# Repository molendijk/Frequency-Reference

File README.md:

# 10MHz Frequency Reference Distributor and 25MHz generator and distributor.

  ## Purpose
  
  This hardware project is intended for people posessing a 10MHz sinusoidal reference oscillator (GPS DO / Rubidium Source) 
  but require a 25MHz reference for use with an SDR (Adalm-Pluto), ADF4351 (Evaluation board) or a 
  LNB (modified Bulls-Eye).
  
  https://www.analog.com/en/resources/evaluation-hardware-and-software/evaluation-boards-kits/adalm-pluto.html
  https://github.com/molendijk/QO100_LO_ADF4351_Loader
  https://3b8mars.org/wp-content/uploads/2023/10/Bulleye-LNB-modification-for-external-clocking-updated-Oct2023.pdf

  ## Implementation

  The circuit first converts the incoming sine-wave to a square-wave. A potentiometer allows to set the square-wave
  duty factor to 50%. This square-wave is then presented to 3 external outputs of which 1 is DC coupled. A 4th internal
  copy is then available internally to be connected to the input of an external 50MHz band-pass filter.
  The 50MHz sinusoidal output of this filter is then connected to the 50MHz input, that is once again transformed to a 
  square-wave and finally divided by 2 to generate 25MHz that is presented to 4 outputs of which 2 are DC coupled.
  
  The circuit also has an interface J6 for the required power supplies (+15V, +5V) for the FE-5650 Rb frequency standard.
  As the FE-5650 module uses a 9 pin Cannon D connector, a special flat-cable with on one side the DB9 F and on the other
  side a 2 x 7 header is needed. The pin correspondances are marked in a table on page 2 of the schematic.
  Note that pin 1 of either connector are aligned (connected).
  
  ## Mounting sequence and Commissioning
  
  ### Preparations
  1. Solder SMD parts on F-side and B-side **EXCEPT: power jumpers R10, R14, R22 and Edge-mount coax connectors**
  2. Solder through-hole parts: potentiometer R15 and U6 regulator, LEDs D1 and D2 (Square pin is the cathode -> short leg).
  ### Power-supply
  3. Connect VBUS to a 16V power-supply and while measuring (with a DVM) the voltage between TP_GND and TP_15V
     trim potentiometer R15 to obtain 15V.
  4. Solder through-hole parts: potentiometers R12, R17 and regulators U2, U3.
  5. Trim potentiometer R17 while measuring TP_P5V to get 5V
  6. Trim potentiometer R12 while measuring TP_P3V3 to get 3.3V
  7. Solder power jumpers: R10, R14 (+5V and +3.3V) and measure the current going into VBUS (IBUS) to be ~30mA. 
  LED D2 should be lit.
  ### 10MHz distributor
  8. Solder Edge-mount SMA coax J1, J2, J3, J4, transistor Q1 and potentiometer R5.
  9. Inject 10MHz ~1.3Vpp in port 10MHz in (J4).
  9. With a DSO (Inputs high-Z) measure the signals at J1, J2 -> ~3.5Vpp AC and J3 -> ~3.5V DC (0 thru +3.5V)
  10. Trim R5 for 50% duty-factor (J1, J2 and J3) Note: V-bias at node C1, R6, R3 will be ~ +1.55V  
  ### 50MHz output
  11. Solder Edge-mount SMA coax J13, through-hole SMA coax: J5, J7, power jumper R22 (+15V, 50MHz gain stage), 
  transistor Q2 and potentiometer R23. 
  12. Connect a previously prepared BPF50 from port BPF50 in (J7) to BPF50 out (J5)
  13. With a DSO (Inputs high-Z) measure the signals on port MHz50 out (J13). -> 50MHz signal ~3.5Vpp AC
  14. Trim R23 for 50% duty-factor 
  ### 25MHz distributor
  15. Solder Edge-mount SMA coax : J9, J10, J11 and J12.
  16. With a DSO (Inputs high-Z) measure the signals on ports J9, J10: 25 MHz DC -> ~3.5V DC (0 thru +3.5V)
  17. With a DSO (Inputs high-Z) measure the signals on ports J11, J12: 25 MHz AC -> ~3.5V AC (50% duty-factor)
 
 Notes: 
  - At the level 17 test configuration IBUS ~0.2A at VBUS +16V
  - Regulator U3 will become hot (70°C) without any heatsink. This may be a good moment to add the heatsink.
  
  18. Connect a flat-cable to J6 and **before connecting the correct Rb reference (FE-5650)**, 
  measure the supply voltages on the DB9 connector.
  
| Pin | Function |
| --- | -------- |
|  1  | +15V     |
|  2  | Gnd +15V |
|  4  | +5V      |
|  5  | Gnd +5V  |
	
  19. Power-down, connect the DB9 side of the flat-cable to the Rb reference, connect the Rb reference 10MHz output
  to J4 the 10MHz input.
  20. Power-up, check supplies, verify and if needed correct the 10MHz 50% duty-factor setting R5. 
  LED D1 should be lit once the Rb reference has reached operating temperature and is frequency locked.
  
  Notes: 
  - The FE-5650 will initially, while heating up, draw >1A from the 15V regulator.
  - The FE-5650 takes a few minutes to heat up and lock to the correct frequency.
  
  ## Trouble shooting
  - In case of no output on the 50MHz port, measure the DC voltages at the outputs of U4 (+3.4V) and U5 (+4.9V).
  If one of these is absent, verify the solder joints of either L1 or L2.
 
  ## Issues with Rev 1.0.0 built 20251031
  - The SMA Edge-mount connector footprints have a greater ground pin spacing than the "standard" Edge-mount SMA
  connectors available. Nevertheless these connectors can be soldered in place, bridging the slight gap between
  the pads and the connector Gnd pins.
  - The TO92 footprint of transistors Q1, Q2 (2N2222) has pin numbering 1,2,3 instead of 3,2,1 (collector emitter swap).
  The workaround is to mount Q1 and Q2 with the flat side opposite to that on the serigraphie.
  - C21 is too close to J6, the 2 x 7 pin header, effectively falling underneath the header plastic. By first mounting
  C21 and then letting the header stick out sufficiently the connector and capacitor can cohabitate.
  - As the 39 nF capacitors are not in the standard series these were replaced by 47 nF capacitors.

  ## Notes
  1. The series terminated DC Coupled outputs are intended to be connected to high-Z (3.3V) logic level inputs.
     The AC Coupled outputs can be terminated in 50 Ohms, typically like when connected to a clock input of an SDR.
  2. The 6th order 50MHz filter is constructed using 3 side-coupled (LC) resonating circuits that yield a good quality factor.
     More details on the construction of this filter will follow soon. 
  3. Certain devices need a sinusoidal 25MHz clock to operate correctly. In this case a simple low-pass filter can
     be used to remove much of the higher harmonics.
  4. Be sure to check permitted input signal levels on 25MHz inputs and if needed, add additional attenuation.

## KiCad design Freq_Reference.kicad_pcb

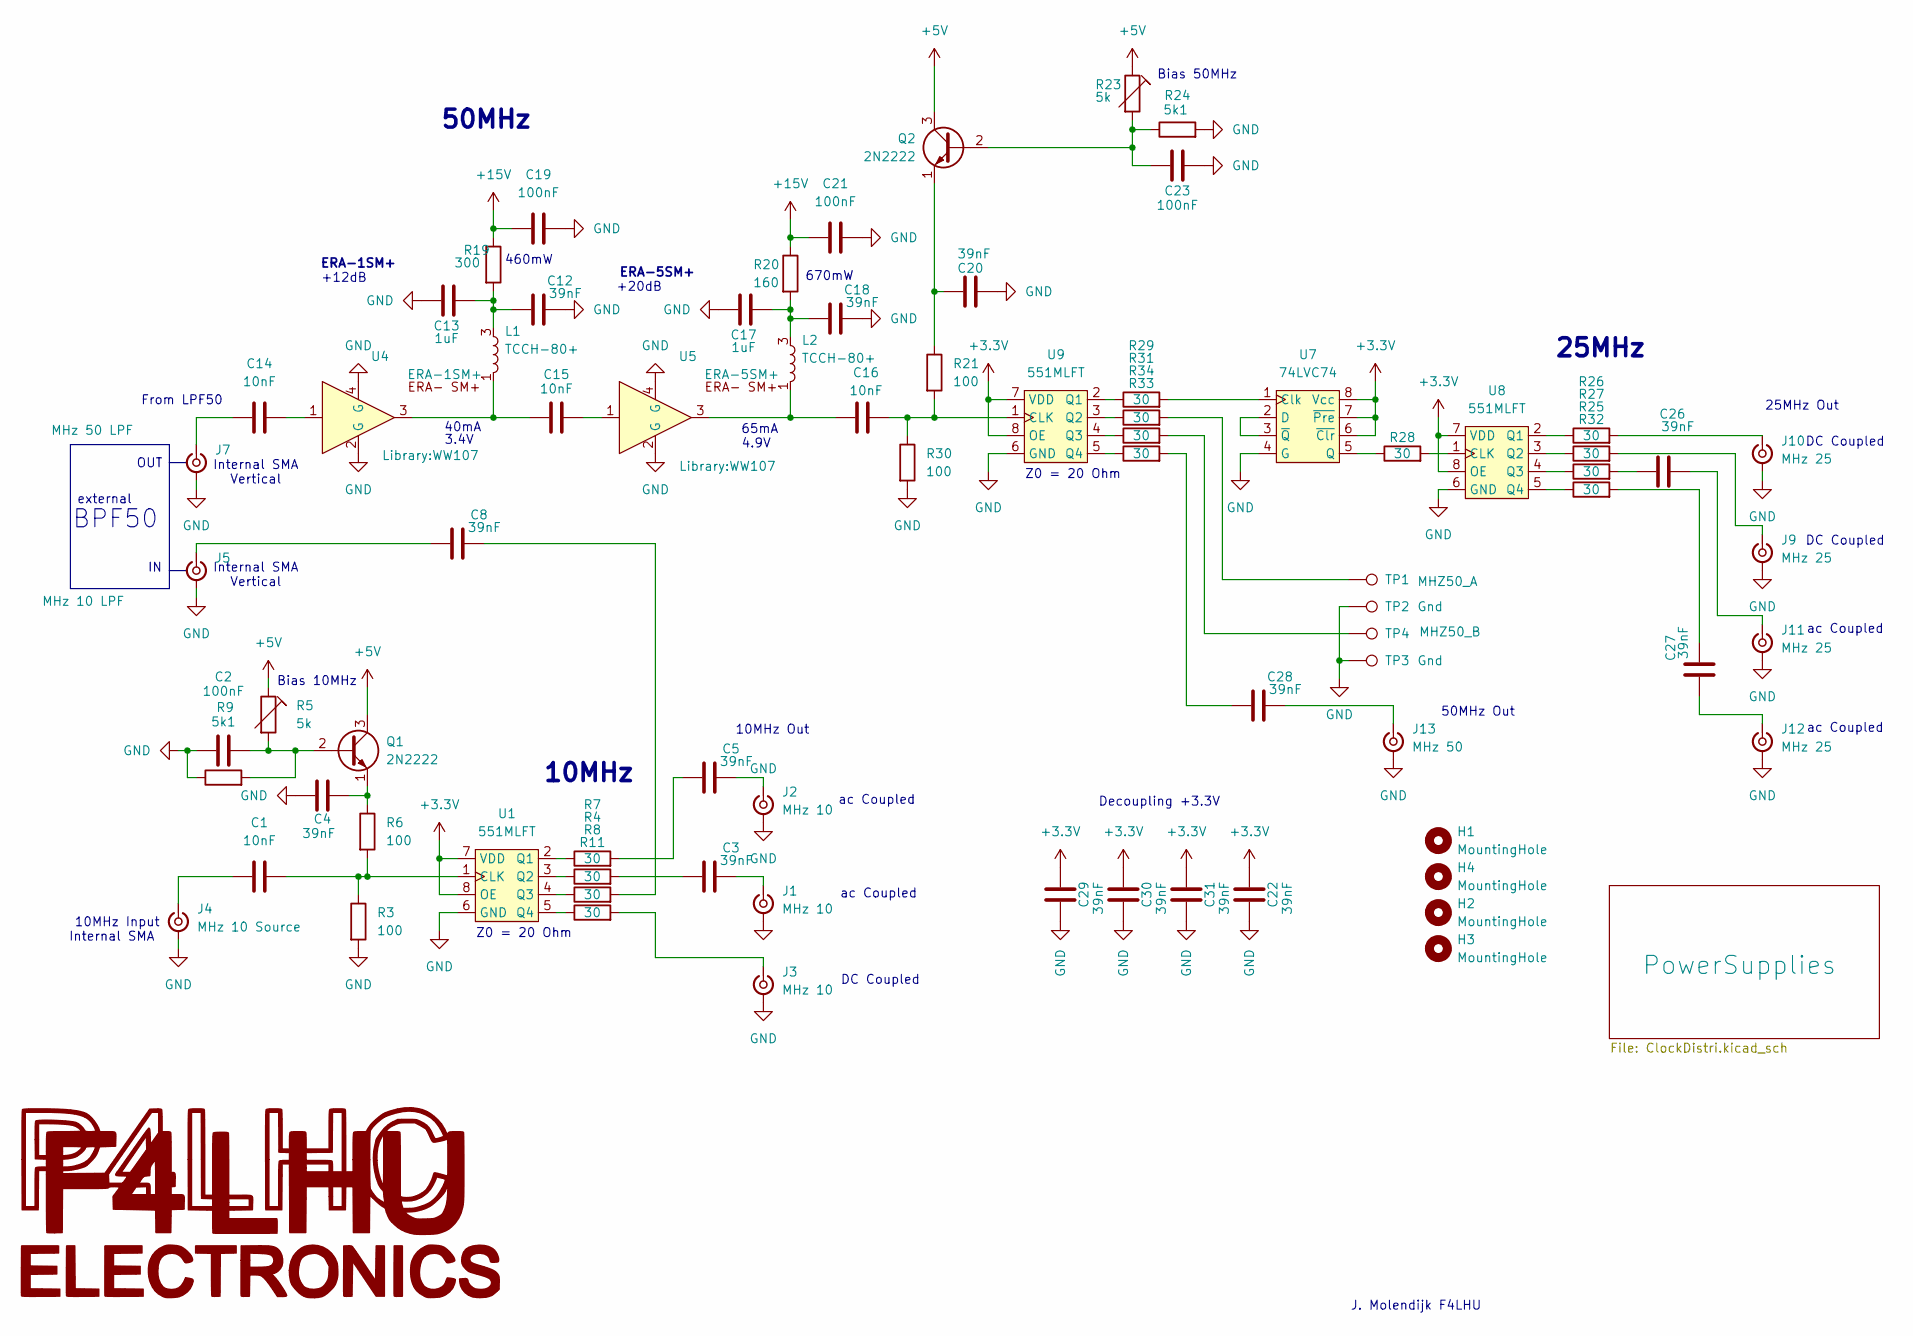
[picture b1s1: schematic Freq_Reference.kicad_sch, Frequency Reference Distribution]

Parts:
C1, C14, C15, C16: 10nF; C_1206_3216Metric_Pad1.33x1.80mm_HandSolder
C2, C19, C21, C23: 100nF; C_1206_3216Metric_Pad1.33x1.80mm_HandSolder
C3, C4, C5, C8, C12, C18, C20, C22, C26, C27, C28, C29, C30, C31: 39nF; C_1206_3216Metric_Pad1.33x1.80mm_HandSolder
C13, C17: 1uF; C_1206_3216Metric_Pad1.33x1.80mm_HandSolder
H1, H2, H3, H4: MountingHole; MountingHole_3.2mm_M3_ISO7380_Pad_TopBottom
J1, J2, J3: MHz 10; SMA_Amphenol_132289_EdgeMount
J4: MHz 10 Source; SMA_Amphenol_132289_EdgeMount
J5: MHz 10 LPF; SMA_Amphenol_132134-11_Vertical
J7: MHz 50 LPF; SMA_Amphenol_132134-11_Vertical
J9, J10, J11, J12: MHz 25; SMA_Amphenol_132289_EdgeMount
J13: MHz 50; SMA_Amphenol_132289_EdgeMount
L1, L2: TCCH-80+; Minicircuits_GU1604
Logo1: LOGO; F4LHU
Q1, Q2: 2N2222; TO-92_Inline_Wide
R3, R6, R21, R30: 100; R_1206_3216Metric_Pad1.30x1.75mm_HandSolder
R4, R7, R8, R11, R25, R26, R27, R28, R29, R31, R32, R33, R34: 30; R_1206_3216Metric_Pad1.30x1.75mm_HandSolder
R5, R23: 5k; Potentiometer_Bourns_3299W_Vertical
R9, R24: 5k1; R_1206_3216Metric_Pad1.30x1.75mm_HandSolder
R19: 300; R_2512_6332Metric_Pad1.40x3.35mm_HandSolder
R20: 160; R_2512_6332Metric_Pad1.40x3.35mm_HandSolder
TP1: MHZ50_A; TestPoint_THTPad_1.5x1.5mm_Drill0.7mm
TP2, TP3: Gnd; TestPoint_THTPad_1.5x1.5mm_Drill0.7mm
TP4: MHZ50_B; TestPoint_THTPad_1.5x1.5mm_Drill0.7mm
U1, U8, U9: 551MLFT; SOIC-8_5.3x6.2mm_P1.27mm
U4: ERA-1SM+; WW107
U5: ERA-5SM+; WW107
U7: 74LVC74; SSOP-8_2.95x2.8mm_P0.65mm

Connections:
+3.3V: C22.1, C29.1, C30.1, C31.1, U1.7 (VDD), U1.8 (OE), U7.6 (~Clr), U7.7 (~Pre), U7.8 (Vcc), U8.7 (VDD), U8.8 (OE), U9.7 (VDD), U9.8 (OE); also elsewhere on the board
+5V: Q1.3 (C), Q2.3 (C), R5.1, R23.1; also elsewhere on the board
+15V: C19.1, C21.1, R19.1, R20.1; also elsewhere on the board
GND: C2.1, C4.2, C12.2, C13.1, C17.1, C18.2, C19.2, C20.2, C21.2, C22.2, C23.2, C29.2, C30.2, C31.2, J1.2 (Ext), J2.2 (Ext), J3.2 (Ext), J4.2 (Ext), J5.2 (Ext), J7.2 (Ext), J9.2 (Ext), J10.2 (Ext), J11.2 (Ext), J12.2 (Ext), J13.2 (Ext), R3.2, R9.1, R24.2, R30.2, TP2.1, TP3.1, U1.6 (GND), U4.2 (G), U4.4 (G), U5.2 (G), U5.4 (G), U7.4 (G), U8.6 (GND), U9.6 (GND); also elsewhere on the board
unnamed: C3.1, R4.2
unnamed: C5.1, R7.2
unnamed: C8.2, R8.2
unnamed: C14.2, U4.1
unnamed: C15.2, U5.1
unnamed: C26.1, R25.2
unnamed: C27.2, R32.2
unnamed: C28.1, R33.2
unnamed: C3.2, J1.1 (In)
unnamed: C5.2, J2.1 (In)
unnamed: J3.1 (In), R11.2
unnamed: C1.1, J4.1 (In)
unnamed: C8.1, J5.1 (In)
unnamed: C14.1, J7.1 (In)
unnamed: J9.1 (In), R27.2
unnamed: J10.1 (In), R26.2
unnamed: C26.2, J11.1 (In)
unnamed: C27.1, J12.1 (In)
unnamed: C28.2, J13.1 (In)
unnamed: C12.1, C13.2, L1.3 (DC), R19.2
unnamed: C15.1, L1.1 (RF-DC), U4.3
unnamed: C17.2, C18.1, L2.3 (DC), R20.2
unnamed: C16.1, L2.1 (RF-DC), U5.3
unnamed: C2.2, Q1.2 (B), R5.2, R9.2
unnamed: C4.1, Q1.1 (E), R6.1
unnamed: C23.1, Q2.2 (B), R23.2, R24.1
unnamed: C20.1, Q2.1 (E), R21.1
unnamed: R31.2, TP1.1
unnamed: R34.2, TP4.1
unnamed: C1.2, R3.1, R6.2, U1.1 (CLK)
unnamed: R7.1, U1.2 (Q1)
unnamed: R4.1, U1.3 (Q2)
unnamed: R8.1, U1.4 (Q3)
unnamed: R11.1, U1.5 (Q4)
unnamed: R29.2, U7.1 (Clk)
unnamed: U7.2 (D), U7.3 (~Q)
unnamed: R28.1, U7.5 (Q)
unnamed: R28.2, U8.1 (CLK)
unnamed: R26.1, U8.2 (Q1)
unnamed: R27.1, U8.3 (Q2)
unnamed: R25.1, U8.4 (Q3)
unnamed: R32.1, U8.5 (Q4)
unnamed: C16.2, R21.2, R30.1, U9.1 (CLK)
unnamed: R29.1, U9.2 (Q1)
unnamed: R31.1, U9.3 (Q2)
unnamed: R34.1, U9.4 (Q3)
unnamed: R33.1, U9.5 (Q4)

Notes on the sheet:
Z0 = 20 Ohm
10MHz Input
Internal SMA
external
BPF50
670mW
10MHz Out
65mA
ac Coupled
40mA
ERA-1SM+
25MHz
DC Coupled
J. Molendijk F4LHU
Decoupling +3.3V
50MHz
From LPF50
3.4V
Internal SMA Vertical
10MHz
Bias 50MHz
+12dB
460mW
4.9V
OUT
Bias 10MHz
ERA-5SM+
25MHz Out
+20dB
50MHz Out

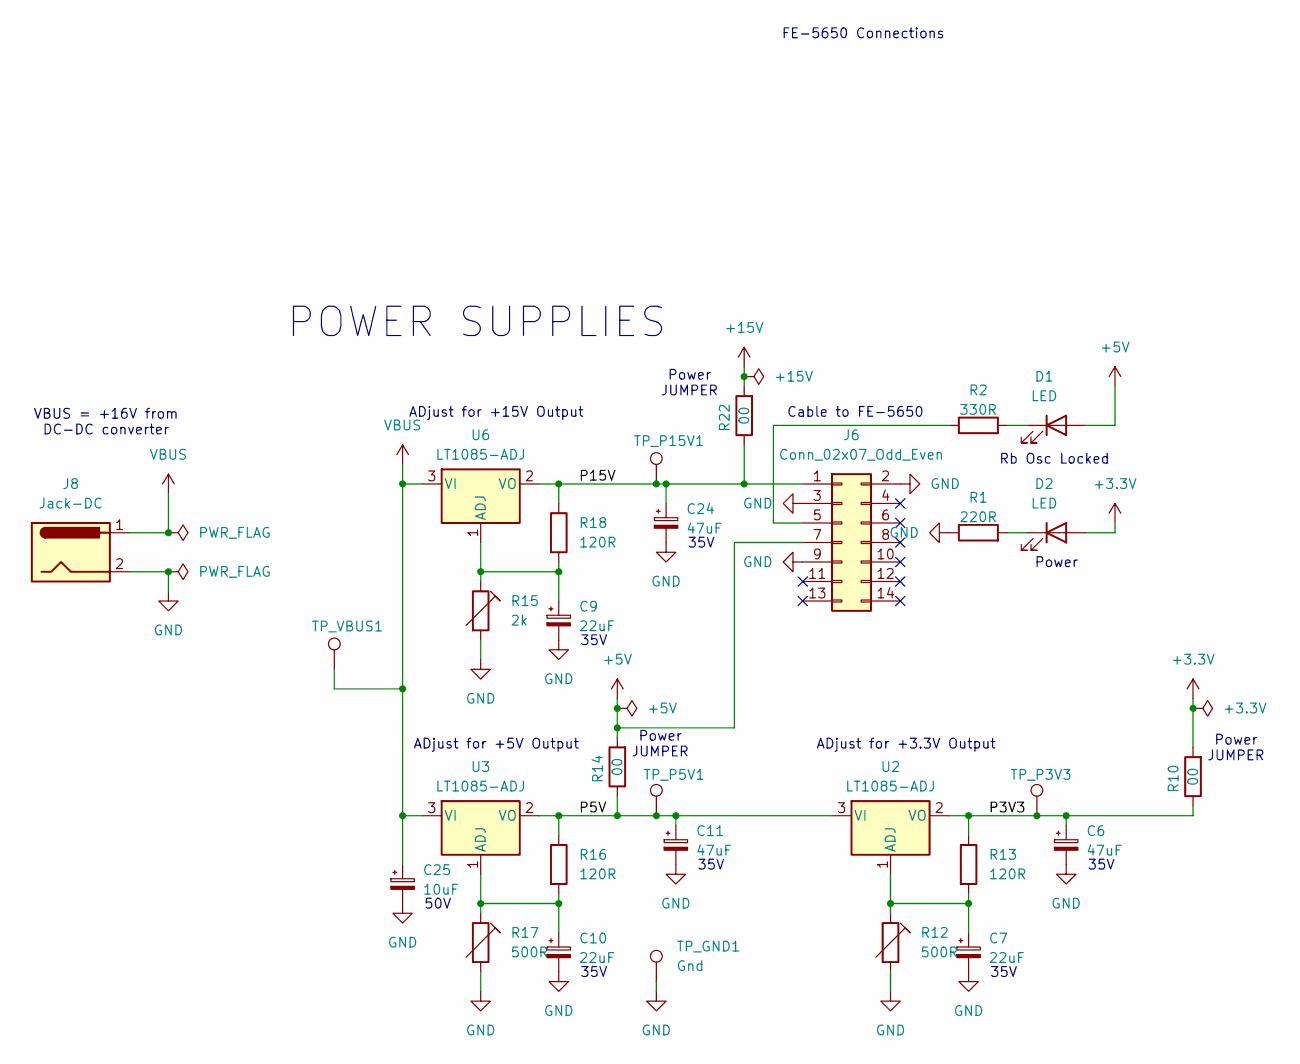
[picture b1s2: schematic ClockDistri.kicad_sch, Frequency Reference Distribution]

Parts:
C6, C11, C24: 47uF; CP_EIA-7343-31_Kemet-D_HandSolder
C7, C9, C10: 22uF; CP_EIA-7343-31_Kemet-D_HandSolder
C25: 10uF; CP_EIA-7343-31_Kemet-D_HandSolder
D1, D2: LED; LED_D3.0mm
J6: Conn_02x07_Odd_Even; PinHeader_2x07_P2.54mm_Vertical
J8: Jack-DC; BarrelJack_Horizontal
R1: 220R; R_1206_3216Metric_Pad1.30x1.75mm_HandSolder
R2: 330R; R_1206_3216Metric_Pad1.30x1.75mm_HandSolder
R10, R14, R22: 00; R_1206_3216Metric_Pad1.30x1.75mm_HandSolder
R12, R17: 500R; Potentiometer_Bourns_3299W_Vertical
R13, R16, R18: 120R; R_1206_3216Metric_Pad1.30x1.75mm_HandSolder
R15: 2k; Potentiometer_Bourns_3299W_Vertical
TP_GND1: Gnd; TestPoint_THTPad_1.5x1.5mm_Drill0.7mm
TP_P3V3: +3.3V; TestPoint_THTPad_1.5x1.5mm_Drill0.7mm
TP_P5V1: +5V; TestPoint_THTPad_1.5x1.5mm_Drill0.7mm
TP_P15V1: +15V; TestPoint_THTPad_1.5x1.5mm_Drill0.7mm
TP_VBUS1: +16V; TestPoint_THTPad_1.5x1.5mm_Drill0.7mm
U2, U3, U6: LT1085-ADJ; TO-220-3_Vertical

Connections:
+3.3V: D2.2 (A), R10.2; also elsewhere on the board
+5V: D1.2 (A), J6.7, R14.2; also elsewhere on the board
+15V: R22.2; also elsewhere on the board
/PowerSupplies/P3V3: C6.1, R10.1, R13.1, TP_P3V3.1, U2.2 (VO)
/PowerSupplies/P5V: C11.1, R14.1, R16.1, TP_P5V1.1, U2.3 (VI), U3.2 (VO)
/PowerSupplies/P15V: C24.1, J6.1, R18.1, R22.1, TP_P15V1.1, U6.2 (VO)
GND: C6.2, C7.2, C9.2, C10.2, C11.2, C24.2, C25.2, J6.2, J6.3, J6.9, J8.2, R1.1, R12.2, R15.2, R17.2, TP_GND1.1; also elsewhere on the board
unnamed: D1.1 (K), R2.2
unnamed: D2.1 (K), R1.2
unnamed: J6.5, R2.1
unnamed: C7.1, R12.1, R13.2, U2.1 (ADJ)
unnamed: C10.1, R16.2, R17.1, U3.1 (ADJ)
unnamed: C9.1, R15.1, R18.2, U6.1 (ADJ)
VBUS: C25.1, J8.1, TP_VBUS1.1, U3.3 (VI), U6.3 (VI)

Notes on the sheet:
35V
50V
Power JUMPER
Power
ADjust for +3.3V Output
POWER SUPPLIES
Cable to FE-5650
ADjust for +5V Output
VBUS = +16V from DC-DC converter
Rb Osc Locked
ADjust for +15V Output
FE-5650 Connections

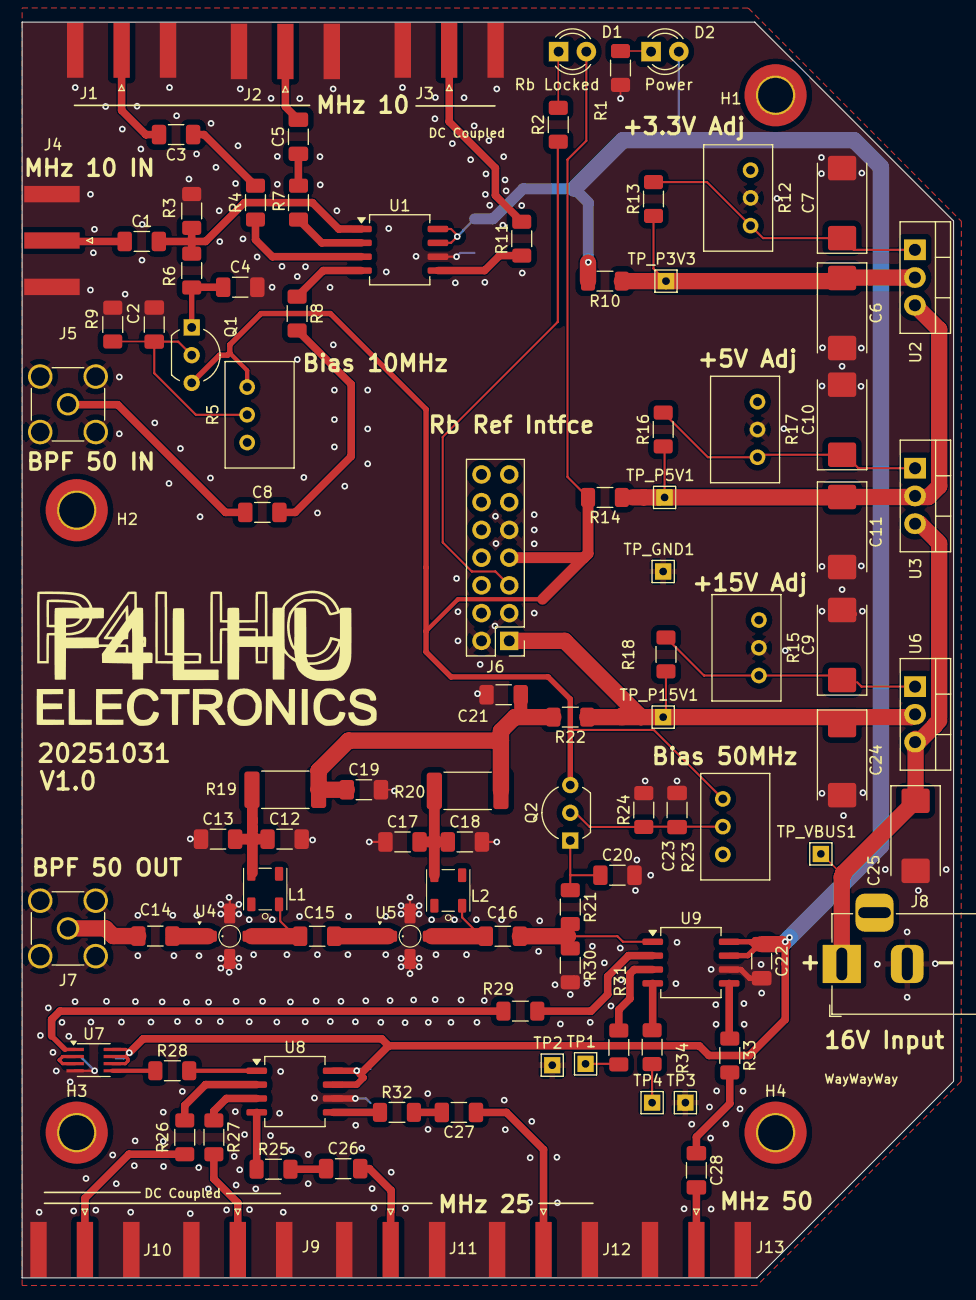
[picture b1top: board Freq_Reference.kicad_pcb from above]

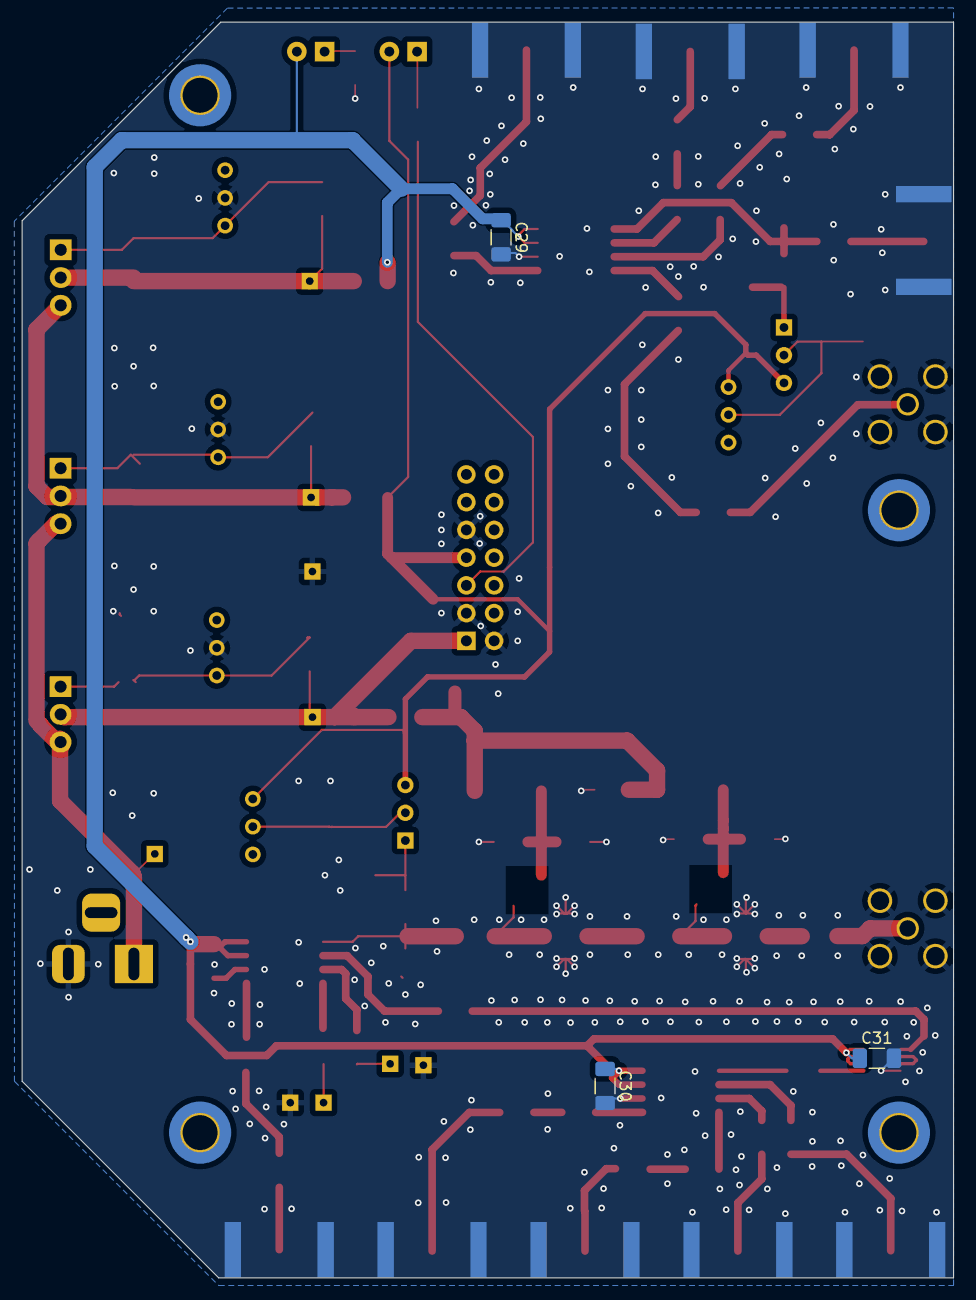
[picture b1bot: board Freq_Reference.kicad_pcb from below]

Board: 2 copper layers, 85.3 x 115.0 mm, 107 parts (3 on the bottom side), 61 nets.

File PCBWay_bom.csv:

Designator,Quantity,Value,Footprint,Package,MPN,DNP,Mount_Type,Description,Sim.Pins
"C1, C14, C15, C16",4,10nF,C_1206_3216Metric_Pad1.33x1.80mm_HandSolder,,,,smt,Unpolarized capacitor,
"C10, C7, C9",3,22uF,CP_EIA-7343-31_Kemet-D_HandSolder,,,,smt,"Polarized capacitor, small symbol",
"C11, C24, C6",3,47uF,CP_EIA-7343-31_Kemet-D_HandSolder,,,,smt,"Polarized capacitor, small symbol",
"C12, C18, C20, C22, C26, C27, C28, C29, C3, C30, C31, C4, C5, C8",14,39nF,C_1206_3216Metric_Pad1.33x1.80mm_HandSolder,,,,smt,Unpolarized capacitor,
"C13, C17",2,1uF,C_1206_3216Metric_Pad1.33x1.80mm_HandSolder,,,,smt,Unpolarized capacitor,
"C19, C2, C21, C23",4,100nF,C_1206_3216Metric_Pad1.33x1.80mm_HandSolder,,,,smt,Unpolarized capacitor,
C25,1,10uF,CP_EIA-7343-31_Kemet-D_HandSolder,,,,smt,"Polarized capacitor, small symbol",
"D1, D2",2,LED,LED_D3.0mm,,,,tht,Light emitting diode,1=K 2=A
"J1, J2, J3",3,MHz 10,SMA_Amphenol_132289_EdgeMount,,,,smt,"small coaxial connector (BNC, SMA, SMB, SMC, Cinch/RCA, LEMO, ...)",
"J10, J11, J12, J9",4,MHz 25,SMA_Amphenol_132289_EdgeMount,,,,smt,"small coaxial connector (BNC, SMA, SMB, SMC, Cinch/RCA, LEMO, ...)",
J13,1,MHz 50,SMA_Amphenol_132289_EdgeMount,,,,smt,"small coaxial connector (BNC, SMA, SMB, SMC, Cinch/RCA, LEMO, ...)",
J4,1,MHz 10 Source,SMA_Amphenol_132289_EdgeMount,,,,smt,"small coaxial connector (BNC, SMA, SMB, SMC, Cinch/RCA, LEMO, ...)",
J5,1,MHz 10 LPF,SMA_Amphenol_132134-11_Vertical,,,,tht,"small coaxial connector (BNC, SMA, SMB, SMC, Cinch/RCA, LEMO, ...)",
J6,1,Conn_02x07_Odd_Even,PinHeader_2x07_P2.54mm_Vertical,,,,tht,"Generic connector, double row, 02x07, odd/even pin numbering scheme (row 1 odd numbers, row 2 even numbers), script generated (kicad-library-utils/schlib/autogen/connector/)",
J7,1,MHz 50 LPF,SMA_Amphenol_132134-11_Vertical,,,,tht,"small coaxial connector (BNC, SMA, SMB, SMC, Cinch/RCA, LEMO, ...)",
J8,1,Jack-DC,BarrelJack_Horizontal,,,,tht,DC Barrel Jack,
"L1, L2",2,TCCH-80+,Minicircuits_GU1604,,,,smt,Inductor,
Logo1,1,LOGO,F4LHU,,,,tht,Logo F4LHU,
"Q1, Q2",2,2N2222,TO-92_Inline_Wide,,,,tht,"0.2A Ic, 40V Vce, Small Signal NPN Transistor, TO-92",
R1,1,220R,R_1206_3216Metric_Pad1.30x1.75mm_HandSolder,,,,smt,Resistor,
"R10, R14, R22",3,00,R_1206_3216Metric_Pad1.30x1.75mm_HandSolder,,,,smt,Resistor,
"R11, R25, R26, R27, R28, R29, R31, R32, R33, R34, R4, R7, R8",13,30,R_1206_3216Metric_Pad1.30x1.75mm_HandSolder,,,,smt,Resistor,
"R12, R17",2,500R,Potentiometer_Bourns_3299W_Vertical,,,,tht,Trimmable resistor (preset resistor),
"R13, R16, R18",3,120R,R_1206_3216Metric_Pad1.30x1.75mm_HandSolder,,,,smt,Resistor,
R15,1,2k,Potentiometer_Bourns_3299W_Vertical,,,,tht,Trimmable resistor (preset resistor),
R19,1,300,R_2512_6332Metric_Pad1.40x3.35mm_HandSolder,,,,smt,Resistor,
R2,1,330R,R_1206_3216Metric_Pad1.30x1.75mm_HandSolder,,,,smt,Resistor,
R20,1,160,R_2512_6332Metric_Pad1.40x3.35mm_HandSolder,,,,smt,Resistor,
"R21, R3, R30, R6",4,100,R_1206_3216Metric_Pad1.30x1.75mm_HandSolder,,,,smt,Resistor,
"R23, R5",2,5k,Potentiometer_Bourns_3299W_Vertical,,,,tht,Trimmable resistor (preset resistor),
"R24, R9",2,5k1,R_1206_3216Metric_Pad1.30x1.75mm_HandSolder,,,,smt,Resistor,
TP1,1,MHZ50_A,TestPoint_THTPad_1.5x1.5mm_Drill0.7mm,,,,tht,test point,
"TP2, TP3, TP_GND1",3,Gnd,TestPoint_THTPad_1.5x1.5mm_Drill0.7mm,,,,tht,test point,
TP4,1,MHZ50_B,TestPoint_THTPad_1.5x1.5mm_Drill0.7mm,,,,tht,test point,
TP_P15V1,1,+15V,TestPoint_THTPad_1.5x1.5mm_Drill0.7mm,,,,tht,test point,
TP_P3V3,1,+3.3V,TestPoint_THTPad_1.5x1.5mm_Drill0.7mm,,,,tht,test point,
TP_P5V1,1,+5V,TestPoint_THTPad_1.5x1.5mm_Drill0.7mm,,,,tht,test point,
TP_VBUS1,1,+16V,TestPoint_THTPad_1.5x1.5mm_Drill0.7mm,,,,tht,test point,
"U1, U8, U9",3,551MLFT,SOIC-8_5.3x6.2mm_P1.27mm,,,,smt,,
"U2, U3, U6",3,LT1085-ADJ,TO-220-3_Vertical,,,,tht,"3.0A 25V LDO Linear Regulator, Adjustable Output, TO-220/TO-263",
U4,1,ERA-1SM+,WW107,,,,smt,,
U5,1,ERA-5SM+,WW107,,,,smt,,
U7,1,74LVC74,SSOP-8_2.95x2.8mm_P0.65mm,,,,smt,,

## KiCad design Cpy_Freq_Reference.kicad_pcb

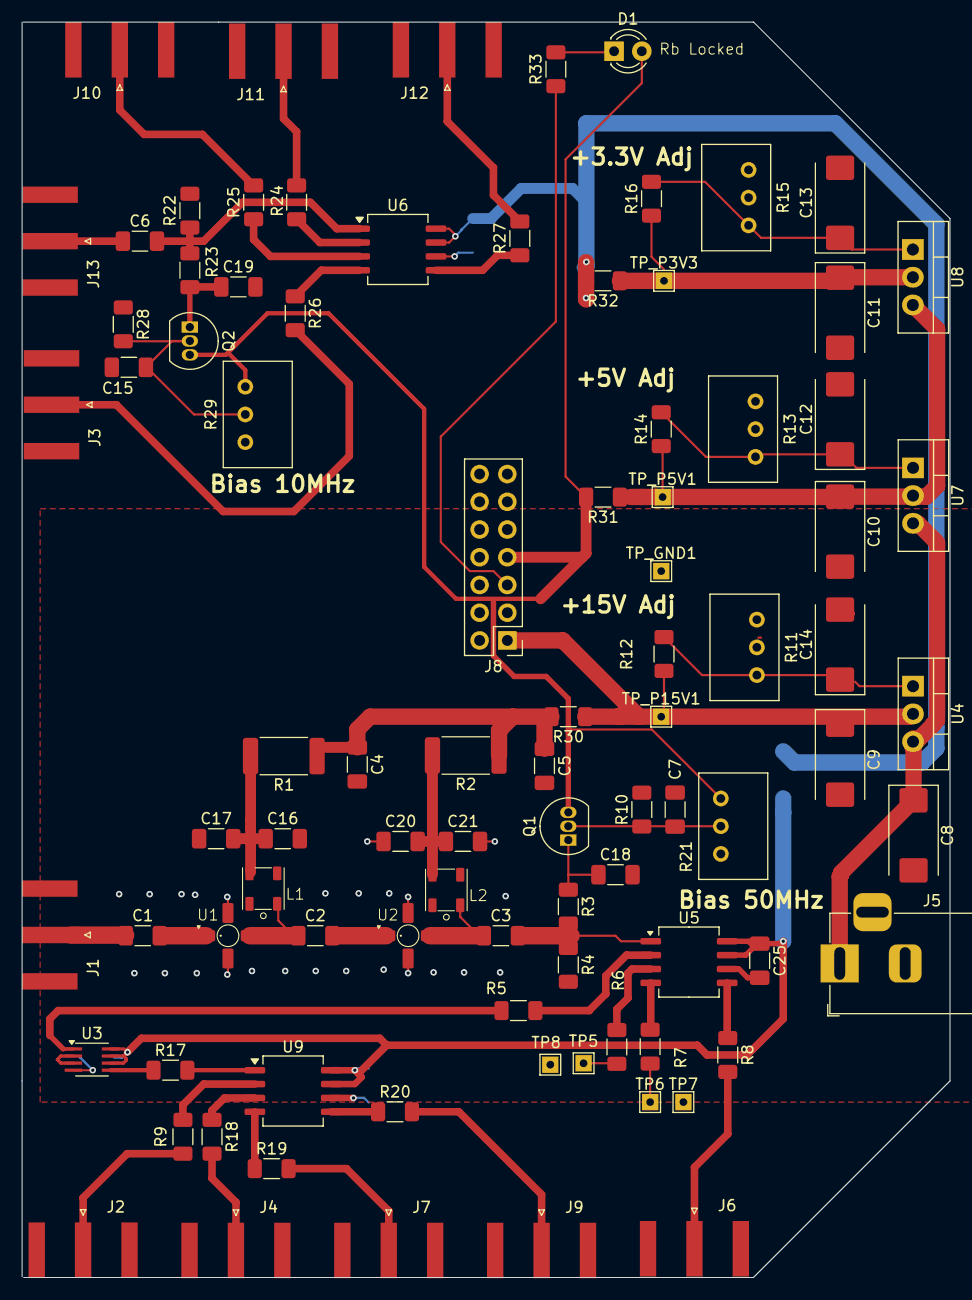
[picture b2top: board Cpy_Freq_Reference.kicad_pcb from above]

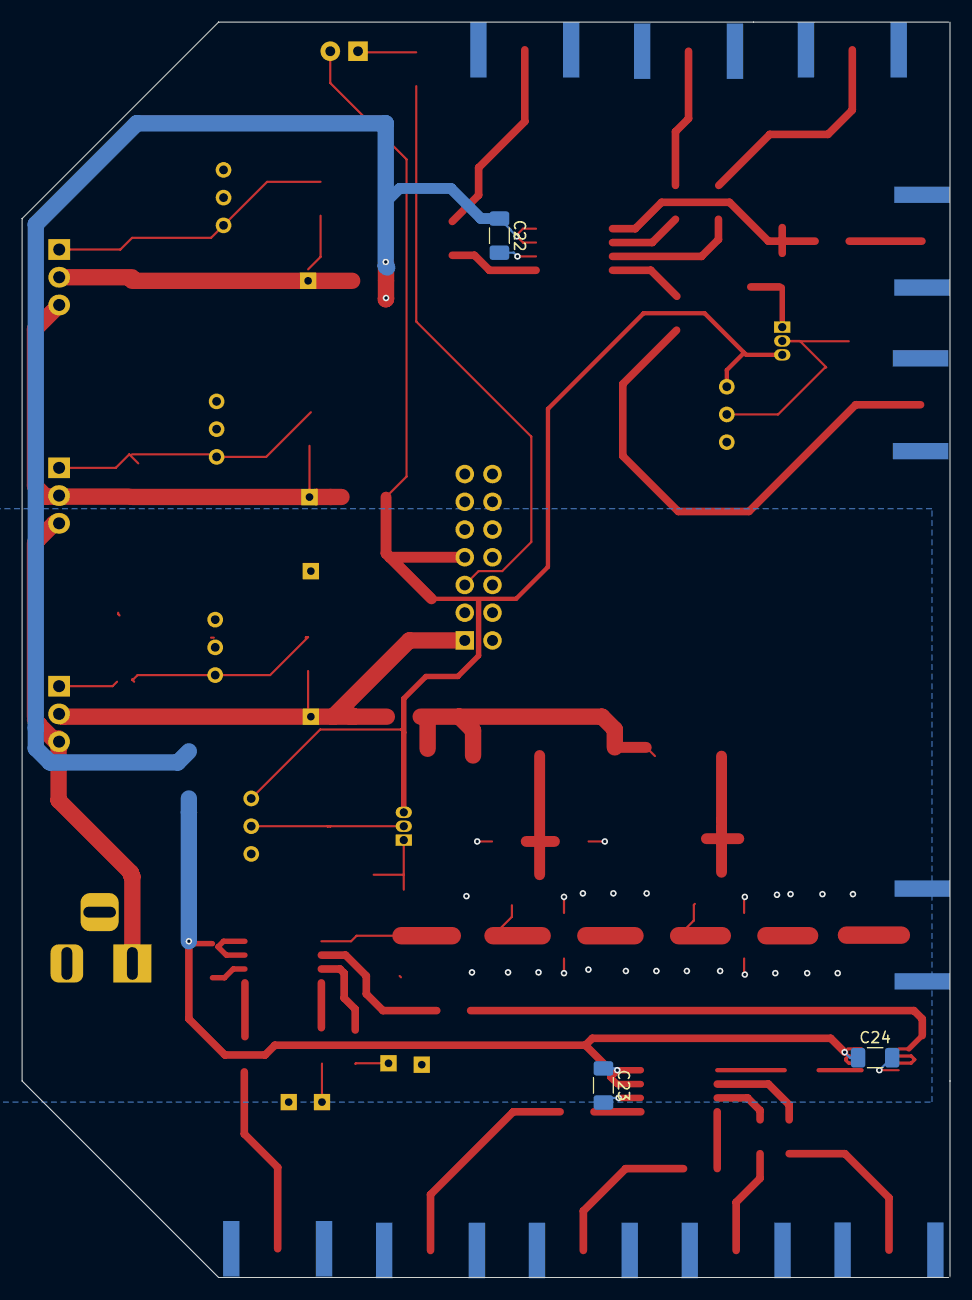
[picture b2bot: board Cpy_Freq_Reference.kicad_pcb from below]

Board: 2 copper layers, 85.0 x 115.0 mm, 93 parts (3 on the bottom side), 54 nets.

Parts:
C1, C2, C3, C6: 10nF; C_1206_3216Metric_Pad1.33x1.80mm_HandSolder
C4, C5, C7, C15: 100nF; C_1206_3216Metric_Pad1.33x1.80mm_HandSolder
C8: 10uF; CP_EIA-7343-31_Kemet-D_HandSolder
C9, C10, C11: 47uF; CP_EIA-7343-31_Kemet-D_HandSolder
C12, C13, C14: 22uF; CP_EIA-7343-31_Kemet-D_HandSolder
C16, C18, C19, C21, C22, C23, C24, C25: 39nF; C_1206_3216Metric_Pad1.33x1.80mm_HandSolder
C17, C20: 1uF; C_1206_3216Metric_Pad1.33x1.80mm_HandSolder
D1: LED; LED_D3.0mm
J1: MHz 50 LPF; SMA_Amphenol_132289_EdgeMount
J2, J4, J7, J9: MHz 25; SMA_Amphenol_132289_EdgeMount
J3: MHz 10 LPF; SMA_Amphenol_132289_EdgeMount
J5: Jack-DC; BarrelJack_Horizontal
J6: MHz 50; SMA_Amphenol_132289_EdgeMount
J8: Conn_02x07_Odd_Even; PinHeader_2x07_P2.54mm_Vertical
J10, J11, J12: MHz 10; SMA_Amphenol_132289_EdgeMount
J13: MHz 10 Source; SMA_Amphenol_132289_EdgeMount
L1, L2: TCCH-80+; Minicircuits_GU1604
Q1, Q2: 2N2222; TO-92_Inline
R1: 300; R_2512_6332Metric_Pad1.40x3.35mm_HandSolder
R2: 160; R_2512_6332Metric_Pad1.40x3.35mm_HandSolder
R3, R4, R22, R23: 100; R_1206_3216Metric_Pad1.30x1.75mm_HandSolder
R5, R6, R7, R8, R9, R17, R18, R19, R20, R24, R25, R26, R27: 30; R_1206_3216Metric_Pad1.30x1.75mm_HandSolder
R10, R28: 5k1; R_1206_3216Metric_Pad1.30x1.75mm_HandSolder
R11: 2k; Potentiometer_Bourns_3299W_Vertical
R12, R14, R16: 120R; R_1206_3216Metric_Pad1.30x1.75mm_HandSolder
R13, R15: 500R; Potentiometer_Bourns_3299W_Vertical
R21, R29: 5k; Potentiometer_Bourns_3299W_Vertical
R30, R31, R32: 00; R_1206_3216Metric_Pad1.30x1.75mm_HandSolder
R33: 330R; R_1206_3216Metric_Pad1.30x1.75mm_HandSolder
TP5: MHZ50_A; TestPoint_THTPad_1.5x1.5mm_Drill0.7mm
TP6: MHZ50_B; TestPoint_THTPad_1.5x1.5mm_Drill0.7mm
TP7, TP8: Gnd; TestPoint_THTPad_1.5x1.5mm_Drill0.7mm
TP_GND1: Gnd; TestPoint_THTPad_1.5x1.5mm_Drill0.7mm
TP_P3V3: +3.3V; TestPoint_THTPad_1.5x1.5mm_Drill0.7mm
TP_P5V1: +5V; TestPoint_THTPad_1.5x1.5mm_Drill0.7mm
TP_P15V1: +15V; TestPoint_THTPad_1.5x1.5mm_Drill0.7mm
U1: 1; WW107
U2: 5; WW107
U3: 74LVC74; SSOP-8_2.95x2.8mm_P0.65mm
U4, U7, U8: LT1085-ADJ; TO-220-3_Vertical
U5, U6, U9: 551MLFT; SOIC-8_5.3x6.2mm_P1.27mm

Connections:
+3.3V: C22.1, C23.1, C24.1, C25.1, R32.2, U3.6 (~Clr), U3.7 (~Pre), U3.8 (Vcc), U5.7 (VDD), U5.8 (OE), U6.7 (VDD), U6.8 (OE), U9.7 (VDD), U9.8 (OE)
+5V: D1.2 (A), J8.7, Q1.3 (C), Q2.3 (C), R21.1, R29.1, R31.2
+15V: C4.1, C5.1, R1.1, R2.1, R30.2
/PowerSupplies/P3V3: C11.1, R16.1, R32.1, TP_P3V3.1, U8.2 (VO)
/PowerSupplies/P5V: C10.1, R14.1, R31.1, TP_P5V1.1, U7.2 (VO), U8.3 (VI)
/PowerSupplies/P15V: C9.1, J8.1, R12.1, R30.1, TP_P15V1.1, U4.2 (VO)
GND: C4.2, C5.2, C7.2, C8.2, C9.2, C10.2, C11.2, C12.2, C13.2, C14.2, C15.1, C16.2, C17.1, C18.2, C19.2, C20.1, C21.2, C22.2, C23.2, C24.2, C25.2, J1.2 (Ext), J2.2 (Ext), J3.2 (Ext), J4.2 (Ext), J5.2, J6.2 (Ext), J7.2 (Ext), J8.2, J8.3, J8.9, J9.2 (Ext), J10.2 (Ext), J11.2 (Ext), J12.2 (Ext), J13.2 (Ext), R4.2, R10.2, R11.2, R13.2, R15.2, R22.2, R28.1, TP7.1, TP8.1, TP_GND1.1, U1.2 (G), U1.4 (G), U2.2 (G), U2.4 (G), U3.4 (G), U5.6 (GND), U6.6 (GND), U9.6 (GND)
unnamed: C1.2, U1.1
unnamed: C2.2, U2.1
unnamed: D1.1 (K), R33.2
unnamed: C1.1, J1.1 (In)
unnamed: J2.1 (In), R9.2
unnamed: J3.1 (In), R26.2
unnamed: J4.1 (In), R18.2
unnamed: J6.1 (In), R8.2
unnamed: J7.1 (In), R19.2
unnamed: J8.5, R33.1
unnamed: J9.1 (In), R20.2
unnamed: J10.1 (In), R25.2
unnamed: J11.1 (In), R24.2
unnamed: J12.1 (In), R27.2
unnamed: C6.1, J13.1 (In)
unnamed: C16.1, C17.2, L1.3 (DC), R1.2
unnamed: C2.1, L1.1 (RF-DC), U1.3
unnamed: C20.2, C21.1, L2.3 (DC), R2.2
unnamed: C3.1, L2.1 (RF-DC), U2.3
unnamed: C7.1, Q1.2 (B), R10.1, R21.2
unnamed: C18.1, Q1.1 (E), R3.1
unnamed: C15.2, Q2.2 (B), R28.2, R29.2
unnamed: C19.1, Q2.1 (E), R23.1
unnamed: R6.2, TP5.1
unnamed: R7.2, TP6.1
unnamed: R5.2, U3.1 (Clk)
unnamed: U3.2 (D), U3.3 (~Q)
unnamed: R17.1, U3.5 (Q)
unnamed: C14.1, R11.1, R12.2, U4.1 (ADJ)
unnamed: C3.2, R3.2, R4.1, U5.1 (CLK)
unnamed: R5.1, U5.2 (Q1)
unnamed: R6.1, U5.3 (Q2)
unnamed: R7.1, U5.4 (Q3)
unnamed: R8.1, U5.5 (Q4)
unnamed: C6.2, R22.1, R23.2, U6.1 (CLK)
unnamed: R24.1, U6.2 (Q1)
unnamed: R25.1, U6.3 (Q2)
unnamed: R26.1, U6.4 (Q3)
unnamed: R27.1, U6.5 (Q4)
unnamed: C12.1, R13.1, R14.2, U7.1 (ADJ)
unnamed: C13.1, R15.1, R16.2, U8.1 (ADJ)
unnamed: R17.2, U9.1 (CLK)
unnamed: R9.1, U9.2 (Q1)
unnamed: R18.1, U9.3 (Q2)
unnamed: R19.1, U9.4 (Q3)
unnamed: R20.1, U9.5 (Q4)
VBUS: C8.1, J5.1, U4.3 (VI), U7.3 (VI)

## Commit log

2025-12-09 Removed unneeded zip archives from git
2025-12-09 Updated with KiCad gitignore suggestions from GitHub
2025-12-09 Initialize README with project details
    Added project overview, purpose, implementation details, and notes.
2025-12-09 Corrected typo
2025-12-10 Added Issues section, extended the Implementation section
2025-12-10 Added Mounting Sequence and Commissioning to README.md
2025-12-10 Added LEDs and some corrections
2025-12-10 Some more corrections
2025-12-12 Added PDFs
2025-12-12 Added Imgs folder
2025-12-12 Added logo
2025-12-12 Added table
2025-12-13 Corrected table format, resized logo
2025-12-13 Corrected table format
2025-12-13 Added links and some additional remarks
2025-12-13 removed file ClockDistri.kicad.sch from project folder
2025-12-13 Restored file ClockDistri.kicad.sch containing powering page
2026-02-02 Added Renesas Clock Buffer data-sheet.
2026-02-02 Now added contents of ClockDistrti.kicad_sch
2026-02-02 Added additional data-sheets
